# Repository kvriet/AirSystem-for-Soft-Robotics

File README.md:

# AirSystem for Soft Robotics
Modular Air System for Soft Robotics\
Designed and created by [C.M. van Riet](https://research.tue.nl/en/persons/cm-katrien-van-riet) - Summer 2025\
With thanks to d.search at Eindhoven University of Technology for their guidance.\
Special thanks to Geert van den Boomen for checking the schematics and debugging the circuits.

## The system

**AirSystem** was designed as a low-cost way to rapidly prototype with air, costing roughly €125 for the entire system. AirSystem consists of 1 controller and 4 pneumatic units. Each pneumatic unit contains one pump, one solenoid valve, and one pressure sensor. The board provides 12V power and as such, any pump or solenoid that requires 12V power can be attached to the unit board. 

### Pneumatic Components
For the pneumatic board, easy-to-find components are used:
1. Pump 370A, 12V, 3.2LPM
2. Solenoid valve Skoocom SC0829GW, 12V
3. MCP-H10 pressure sensor, 0-200kPa, 3.3V

### Manual
A manual for AirSystem describes in detail how the system works and how the Arduino library can be installed: [AirSystem Manual](https://github.com/kvriet/AirSystem-for-Soft-Robotics/blob/main/Air%20System%20manual%20v1.4.pdf)
Users are free to connect the sensor, pump, and valve to their inflatables as desired. However, a sample pneumatic circuit is outlined in the manual, along with example Arduino sketches that work well with such a circuit.

## Arduino Library
The system is controlled by a Waveshare RP2040 Zero and can be programmed through the Arduino IDE with a custom library: [AirSystem](https://github.com/kvriet/AirSystem-for-Soft-Robotics/tree/main/Arduino%20library/AirSystem) This folder should be placed in the libraries folder of the Arduino folder. 

The library comes with 7 examples that showcase the abilities of **AirSystem**:
  1. Manual control
  2. Pressure reading
  3. Pump control
  4. Valve control
  5. Pump control without delay
  6. Haptic effects
  7. Object arrays

The video below shows such a haptic effect:

## Schematics and KiCAD Files
The schematics for this project and the KiCAD files can be found here: [KiCAD folder](https://github.com/kvriet/AirSystem-for-Soft-Robotics/tree/main/KiCAD).

## 3D Printing Files
The STLs for this project can be found here: [Design Files](https://github.com/kvriet/AirSystem-for-Soft-Robotics/tree/main/Design%20Files).
- The prints will fit most regular printers and can be printed out of PLA, 0.3 layer height, 4 perimeters (walls), 20% infill. The cushions for the pumps and solenoids are printed in TPU. These cushions can be replaced with some sponge (simple kitchen sponges work well) if TPU printing is not an option.
- To minimise vibrations and prevent the cases from sliding around on a hard surface, 6mm silicone feet are added to the bottom of control and follower cases.
- Any 4mm holes in the prints will require M3x4mm heated inserts to create screw holes. These can be inserted with a soldering iron at roughly 300 degrees Celsius. The other 3mm holes are self-tapping.

The screws needed for these cases are:

**Controller**
- 4x M3x10 or M3x20 (any length in between), flathead

**Follower**
- 4x M3x6 for the coloured cover
- 4x M3 spacer: 6mm height, 6mm thread
- 8x M3x10 for the clamps

## Limitations
- Although protection is implemented on the signal lines, the Waveshare RP2040 Zero sometimes dies when the IDC connector cable is plugged into the controller or follower when the RP2040 is still connected by USB C. For this reason, it is important to unplug the RP2040 before plugging in/out ribbon cables.
- Due to the above issue, I am looking into switching to the ESP32 C3 Zero (Pro). This board is equally cheap, but seems to be more robust. This board is currently not yet a drop-in replacement for the RP2040, although it can already be made to work if some soldering on the controller is reworked and the pin numbers in the library are updated. I will probably release KiCAD files for an ESP32 controller in the future. The follower boards will not be affected, although the resistor value in series with the mosfet might be updated (from 1k to 500R).
- The Skoocom solenoid valve is able to remain closed up to pressures of 100kPa, whereas the pump is able to deliver 150kPa. This means the valve will start leaking at pressures over 100kPa. In practice, this is not a major issue, as our projects rarely need pressures of over 100kPa (usually maxing out at 50kPa for haptic purposes). However, this overpressure might reduce valve longevity in the long run. In the future, a higher-pressure solenoid valve could be found, or a pump could be found that delivers max 100kPa. This would also allow for a lower-range pressure sensor to be used, the MCP-H10 0-100kPa, 3.3V. Switching to the 0-100kPa sensor would also double pressure measuring resolution.
- Currently no PID has been implemented in the library. As many inflatables or the tubing used are somewhat elastic, I have found that setting a target pressure (feedback loop sensor reading to pump power) is enough to achieve that pressure with a minimal offset. However, for more high-end applications, PID should be implemented.
- The Skoocom solenoid valve is not proportional. It is just open/closed. This means that controller deflation is a challenge. This can be worked around by turning on the pump simultaneously to opening the valve to reduce the air flowing out. Additionally, a resistor (very thin tube) could be connected to the valve outlet to reduce airflow out of the system. However, such a resistor also slows down response times when air does need to evacuate the system quickly. This is a trade-off for how cheap this entire system is.

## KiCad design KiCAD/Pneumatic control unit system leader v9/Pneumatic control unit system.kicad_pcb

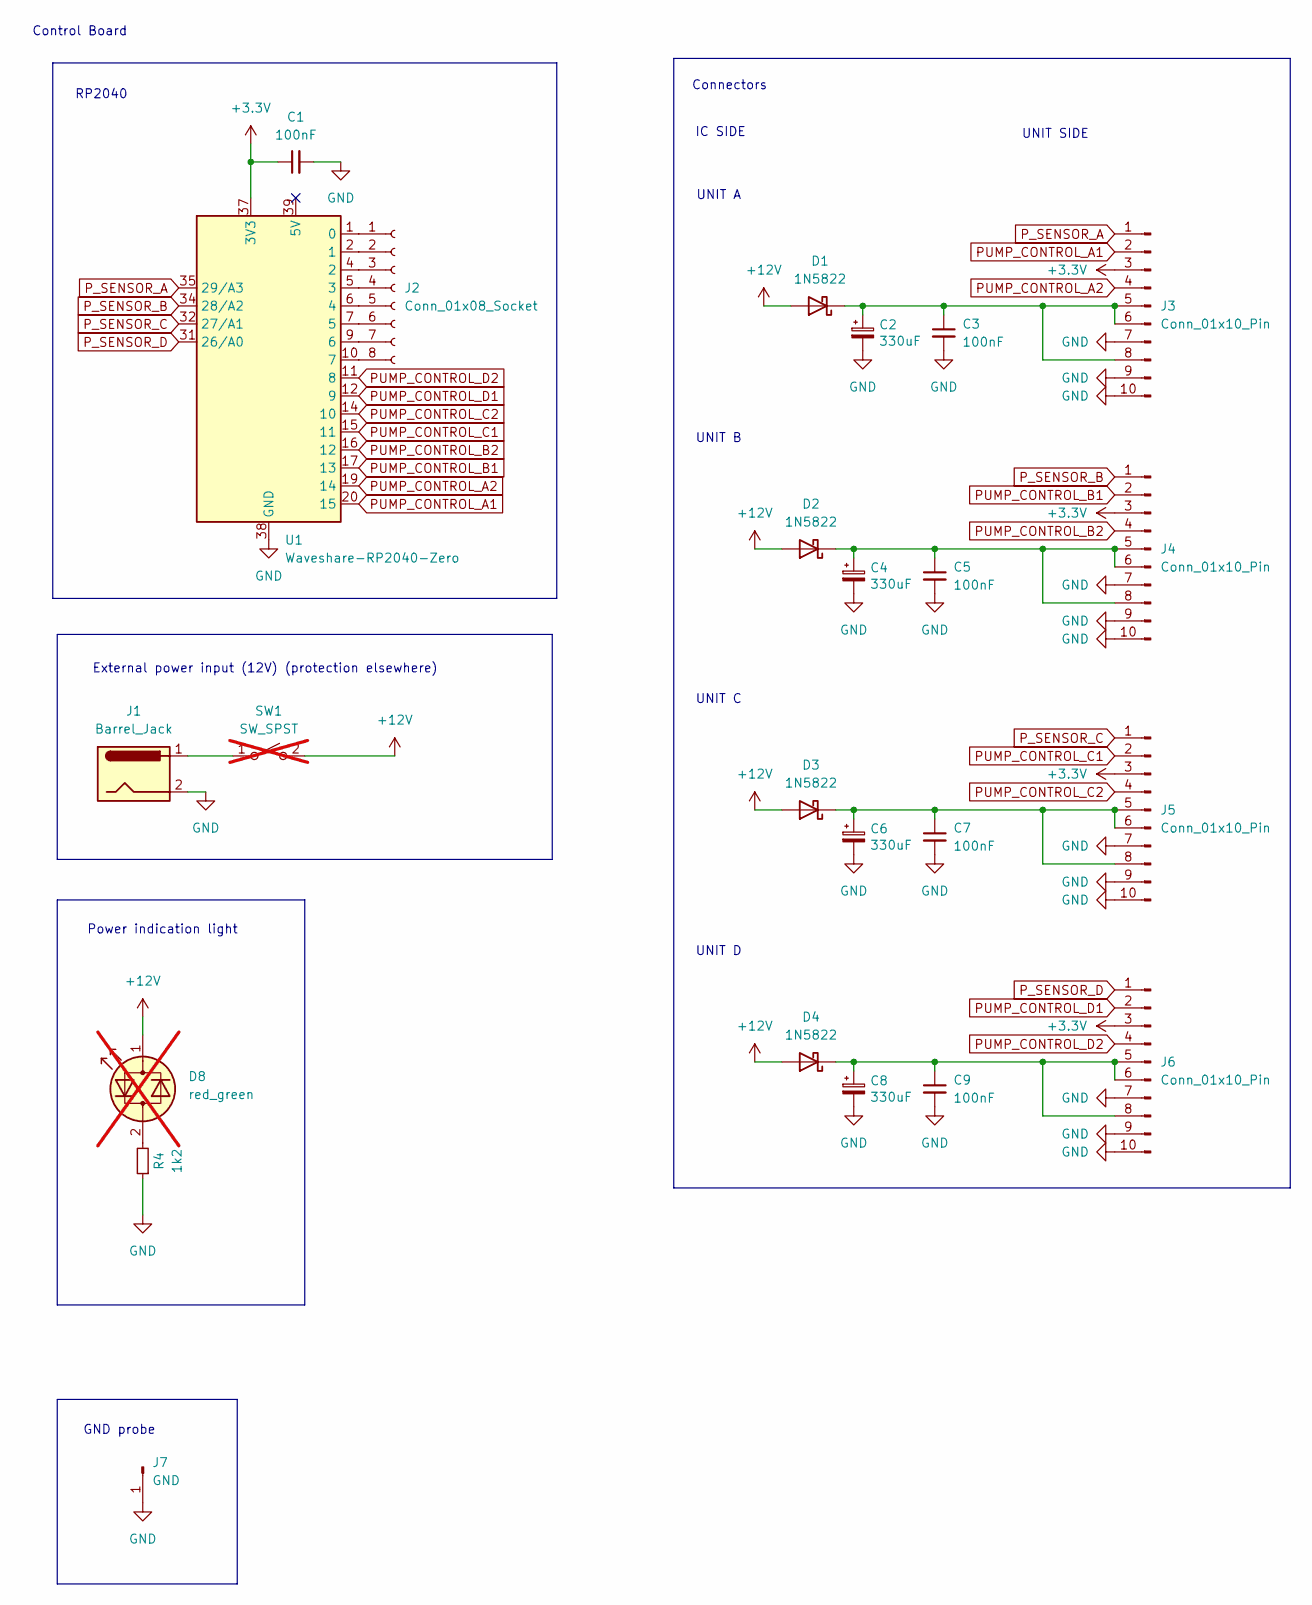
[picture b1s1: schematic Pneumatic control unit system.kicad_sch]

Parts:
C1, C3, C5, C7, C9: 100nF; C_0603_1608Metric_Pad1.08x0.95mm_HandSolder
C2, C4, C6, C8: 330uF; CP_Radial_D10.0mm_P5.00mm
D1, D2, D3, D4: 1N5822; D_DO-201AD_P15.24mm_Horizontal
D8: red_green; PinHeader_1x02_P2.54mm_Vertical; not fitted
J1: Barrel_Jack; BarrelJack_Horizontal
J2: Conn_01x08_Socket; PinHeader_1x08_P2.54mm_Vertical
J3, J4, J5, J6: Conn_01x10_Pin; IDC-Header_2x05_P2.54mm_Vertical
J7: GND; TestPoint_Loop_D2.50mm_Drill1.0mm
R4: 1k2; R_0805_2012Metric_Pad1.20x1.40mm_HandSolder
SW1: SW_SPST; PinHeader_1x02_P2.54mm_Vertical; not fitted
U1: Waveshare-RP2040-Zero; Waveshare_RP2040_Zero

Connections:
+3.3V: C1.1, J3.3, J4.3, J5.3, J6.3, U1.37 (3V3)
+12V: D1.2 (A), D2.2 (A), D3.2 (A), D4.2 (A), D8.1 (KA), SW1.2 (B)
GND: C1.2, C2.2, C3.2, C4.2, C5.2, C6.2, C7.2, C8.2, C9.2, J1.2, J3.7, J3.9, J3.10, J4.7, J4.9, J4.10, J5.7, J5.9, J5.10, J6.7, J6.9, J6.10, J7.1, R4.1, U1.38 (GND); also elsewhere on the board
unnamed: C2.1, C3.1, D1.1 (K), J3.5, J3.6, J3.8
unnamed: C4.1, C5.1, D2.1 (K), J4.5, J4.6, J4.8
unnamed: C6.1, C7.1, D3.1 (K), J5.5, J5.6, J5.8
unnamed: C8.1, C9.1, D4.1 (K), J6.5, J6.6, J6.8
unnamed: D8.2 (AK), R4.2
unnamed: J2.1, U1.1 (0)
unnamed: J2.2, U1.2 (1)
unnamed: J2.3, U1.4 (2)
unnamed: J2.4, U1.5 (3)
unnamed: J2.5, U1.6 (4)
unnamed: J2.6, U1.7 (5)
unnamed: J2.7, U1.9 (6)
unnamed: J2.8, U1.10 (7)
unnamed: J1.1, SW1.1 (A)
PUMP_CONTROL_A1: J3.2, U1.20 (15)
PUMP_CONTROL_A2: J3.4, U1.19 (14)
PUMP_CONTROL_B1: J4.2, U1.17 (13)
PUMP_CONTROL_B2: J4.4, U1.16 (12)
PUMP_CONTROL_C1: J5.2, U1.15 (11)
PUMP_CONTROL_C2: J5.4, U1.14 (10)
PUMP_CONTROL_D1: J6.2, U1.12 (9)
PUMP_CONTROL_D2: J6.4, U1.11 (8)
P_SENSOR_A: J3.1, U1.35 (29/A3)
P_SENSOR_B: J4.1, U1.34 (28/A2)
P_SENSOR_C: J5.1, U1.32 (27/A1)
P_SENSOR_D: J6.1, U1.31 (26/A0)

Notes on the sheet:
UNIT D
UNIT SIDE
Power indication light
UNIT C
External power input (12V) (protection elsewhere)
UNIT A
RP2040
Connectors
IC SIDE
Control Board
UNIT B
GND probe

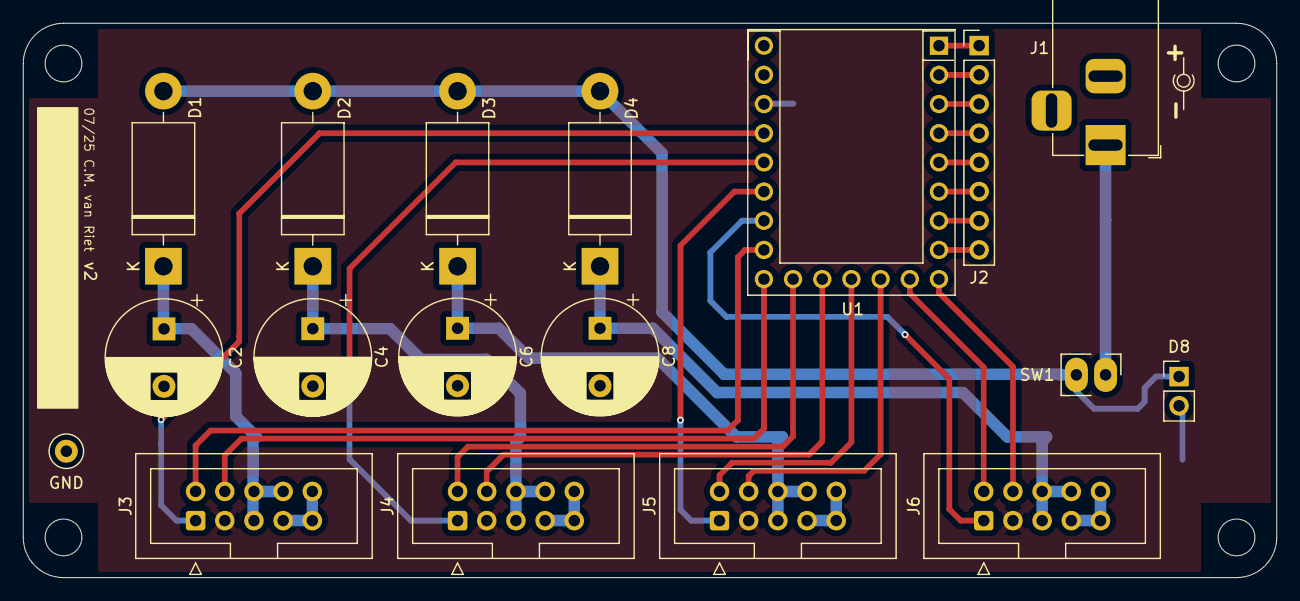
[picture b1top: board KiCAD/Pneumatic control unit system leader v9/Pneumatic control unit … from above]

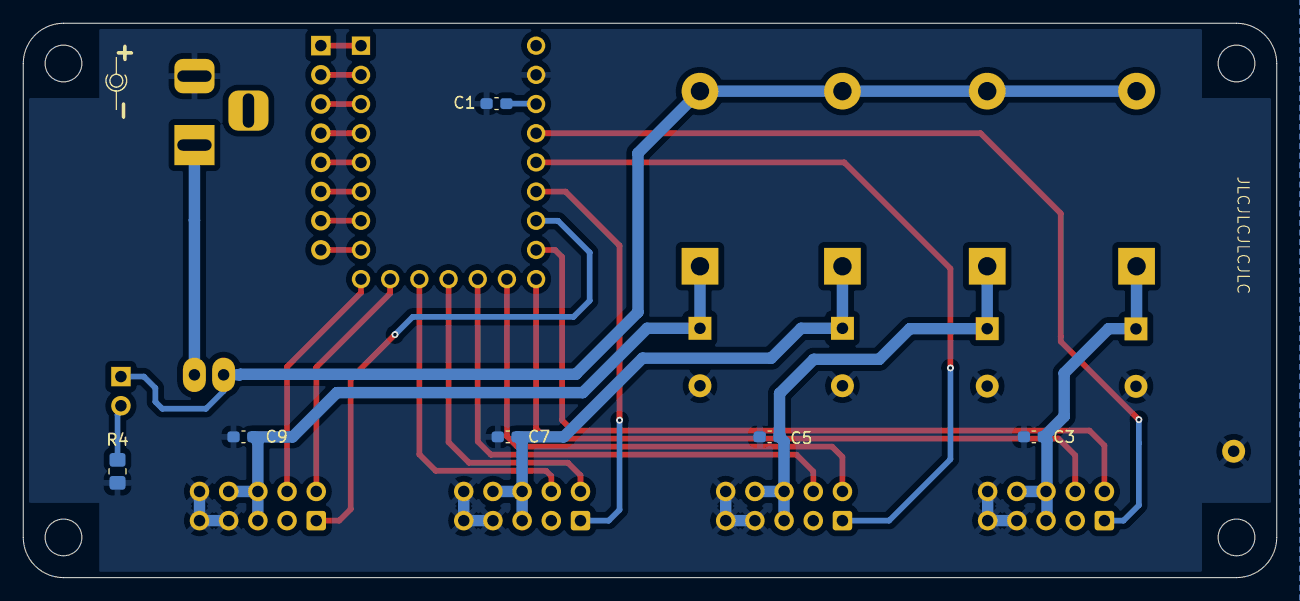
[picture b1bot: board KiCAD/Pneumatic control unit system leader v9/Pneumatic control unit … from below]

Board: 2 copper layers, 109.1 x 48.2 mm, 24 parts (6 on the bottom side), 29 nets.

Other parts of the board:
GND: GND; TestPoint_Loop_D2.50mm_Drill1.0mm

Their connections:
GND: GND.1; also elsewhere on the board

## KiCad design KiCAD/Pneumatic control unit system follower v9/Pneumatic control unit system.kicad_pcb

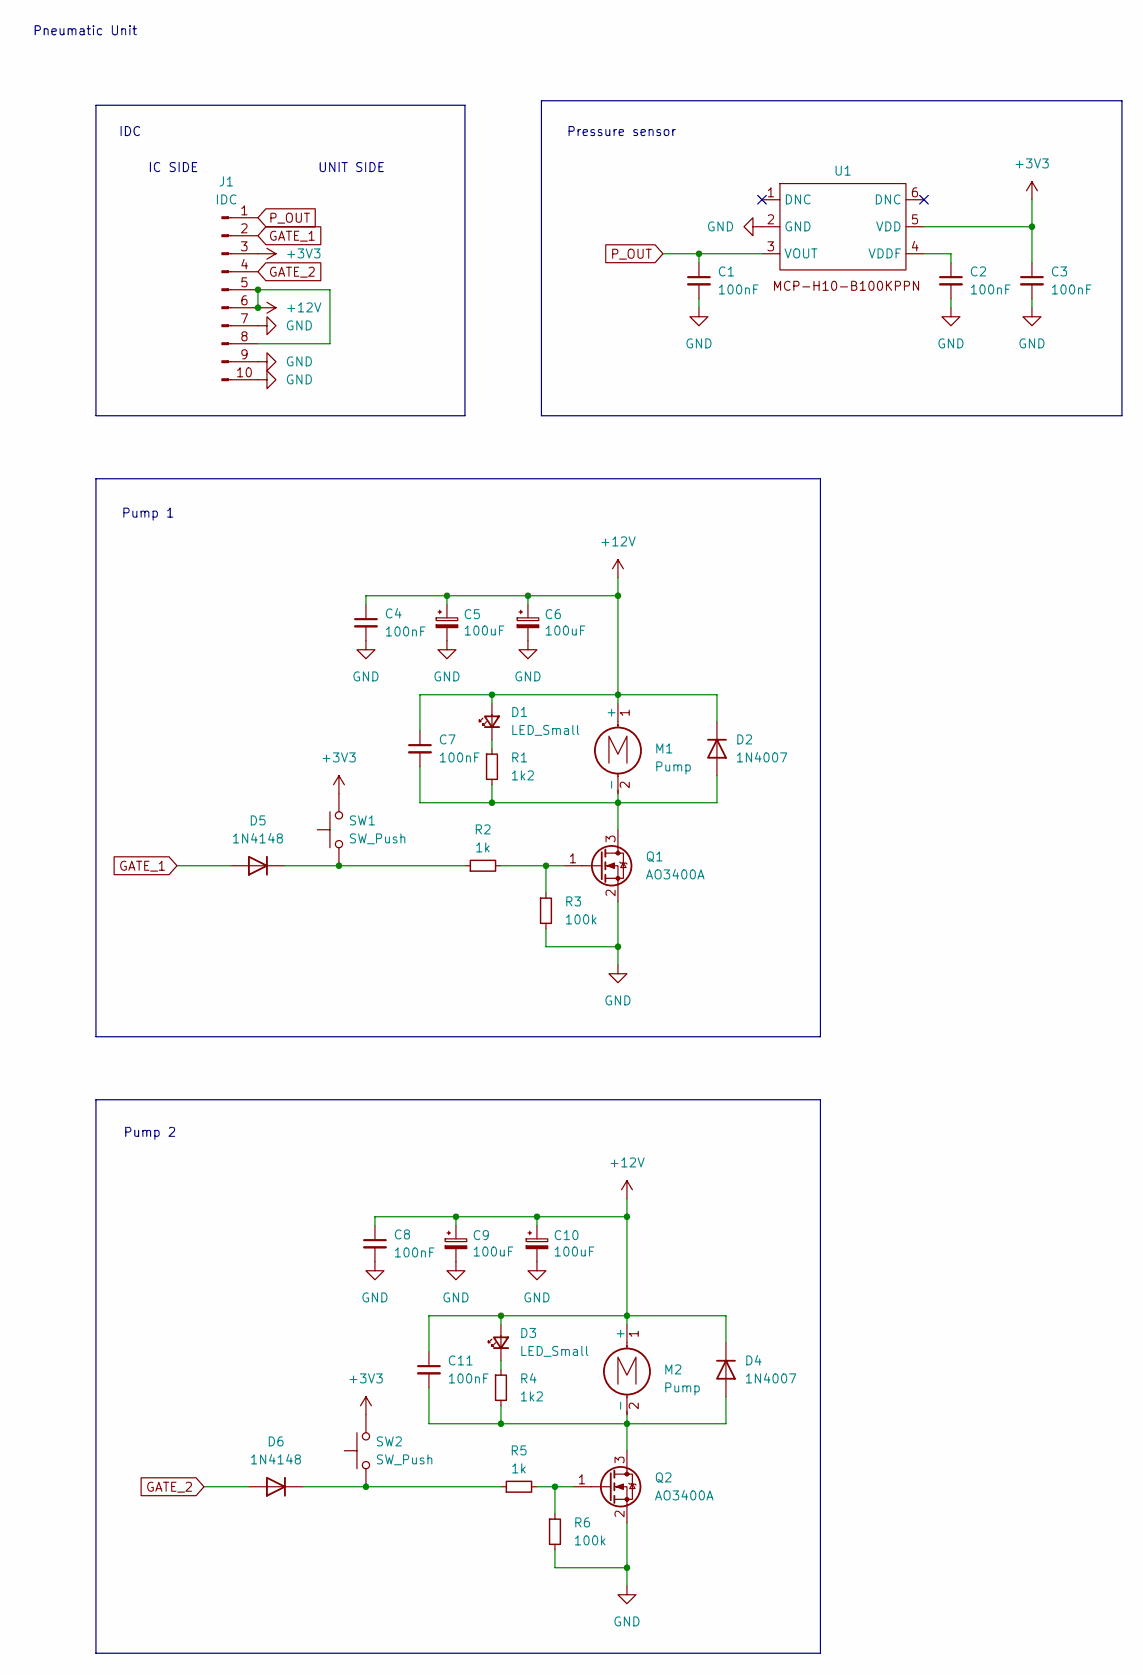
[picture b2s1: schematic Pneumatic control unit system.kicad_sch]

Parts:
C1, C2, C3, C4, C7, C8, C11: 100nF; C_0603_1608Metric_Pad1.08x0.95mm_HandSolder
C5, C6, C9, C10: 100uF; CP_Radial_D6.3mm_P2.50mm
D1, D3: LED_Small; D_0805_2012Metric_Pad1.15x1.40mm_HandSolder
D2, D4: 1N4007; D_DO-41_SOD81_P10.16mm_Horizontal
D5, D6: 1N4148; D_DO-35_SOD27_P7.62mm_Horizontal
J1: IDC; IDC-Header_2x05_P2.54mm_Vertical
M1, M2: Pump; TerminalBlock_Phoenix_MPT-0,5-2-2.54_1x02_P2.54mm_Horizontal
Q1, Q2: AO3400A; SOT-23
R1, R4: 1k2; R_0603_1608Metric_Pad0.98x0.95mm_HandSolder
R2, R5: 1k; R_0603_1608Metric_Pad0.98x0.95mm_HandSolder
R3, R6: 100k; R_0603_1608Metric_Pad0.98x0.95mm_HandSolder
SW1, SW2: SW_Push; SW_PUSH_6mm
U1: MCP-H10

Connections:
+3V3: C3.1, J1.3, SW1.2, SW2.2, U1.5 (VDD)
+12V: C4.1, C5.1, C6.1, C7.1, C8.1, C9.1, C10.1, C11.1, D1.2 (A), D2.1 (K), D3.2 (A), D4.1 (K), J1.5, J1.6, J1.8, M1.1 (+), M2.1 (+)
GATE_1: D5.2 (A), J1.2
GATE_2: D6.2 (A), J1.4
GND: C1.2, C2.2, C3.2, C4.2, C5.2, C6.2, C8.2, C9.2, C10.2, J1.7, J1.9, J1.10, Q1.2 (S), Q2.2 (S), R3.2, R6.2, U1.2 (GND); also elsewhere on the board
unnamed: D1.1 (K), R1.1
unnamed: C7.2, D2.2 (A), M1.2 (-), Q1.3 (D), R1.2
unnamed: D3.1 (K), R4.1
unnamed: C11.2, D4.2 (A), M2.2 (-), Q2.3 (D), R4.2
unnamed: D5.1 (K), R2.1, SW1.1
unnamed: D6.1 (K), R5.1, SW2.1
unnamed: Q1.1 (G), R2.2, R3.1
unnamed: Q2.1 (G), R5.2, R6.1
unnamed: C2.1, U1.4 (VDDF)
P_OUT: C1.1, J1.1, U1.3 (VOUT)

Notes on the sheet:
Pump 2
IC SIDE
Pneumatic Unit
Pump 1
IDC
UNIT SIDE
Pressure sensor

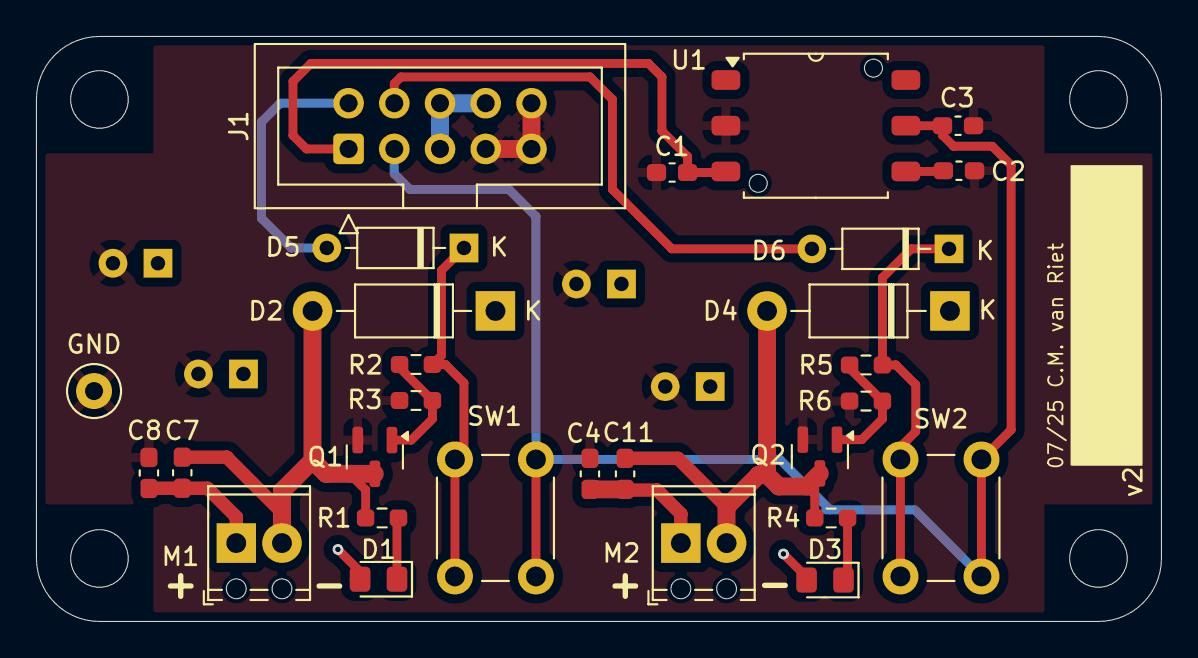
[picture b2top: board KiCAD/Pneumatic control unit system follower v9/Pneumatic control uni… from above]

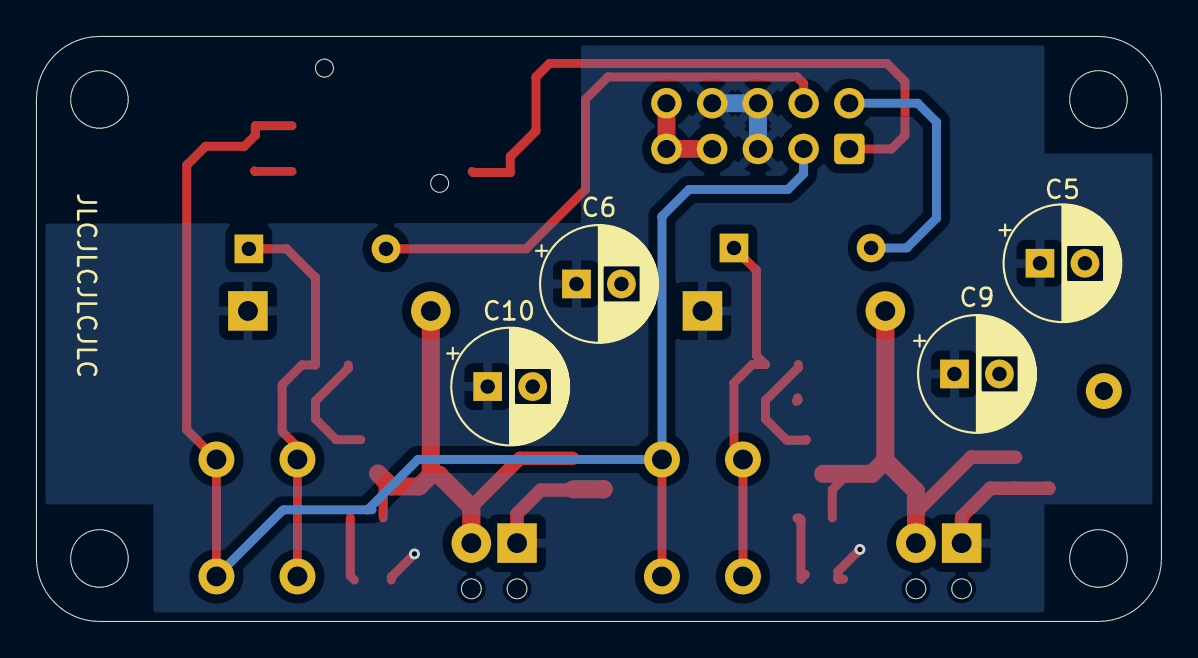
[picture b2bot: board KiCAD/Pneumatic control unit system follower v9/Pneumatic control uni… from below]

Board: 2 copper layers, 62.5 x 32.5 mm, 32 parts (4 on the bottom side), 15 nets.

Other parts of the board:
GND: TestPoint_Loop_D2.50mm_Drill1.0mm

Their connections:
GND: GND.1; also elsewhere on the board

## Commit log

2025-09-27 first upload
2025-09-27 renamed file
2025-09-28 added schematics
2026-05-11 updated manual and first demo sketch
